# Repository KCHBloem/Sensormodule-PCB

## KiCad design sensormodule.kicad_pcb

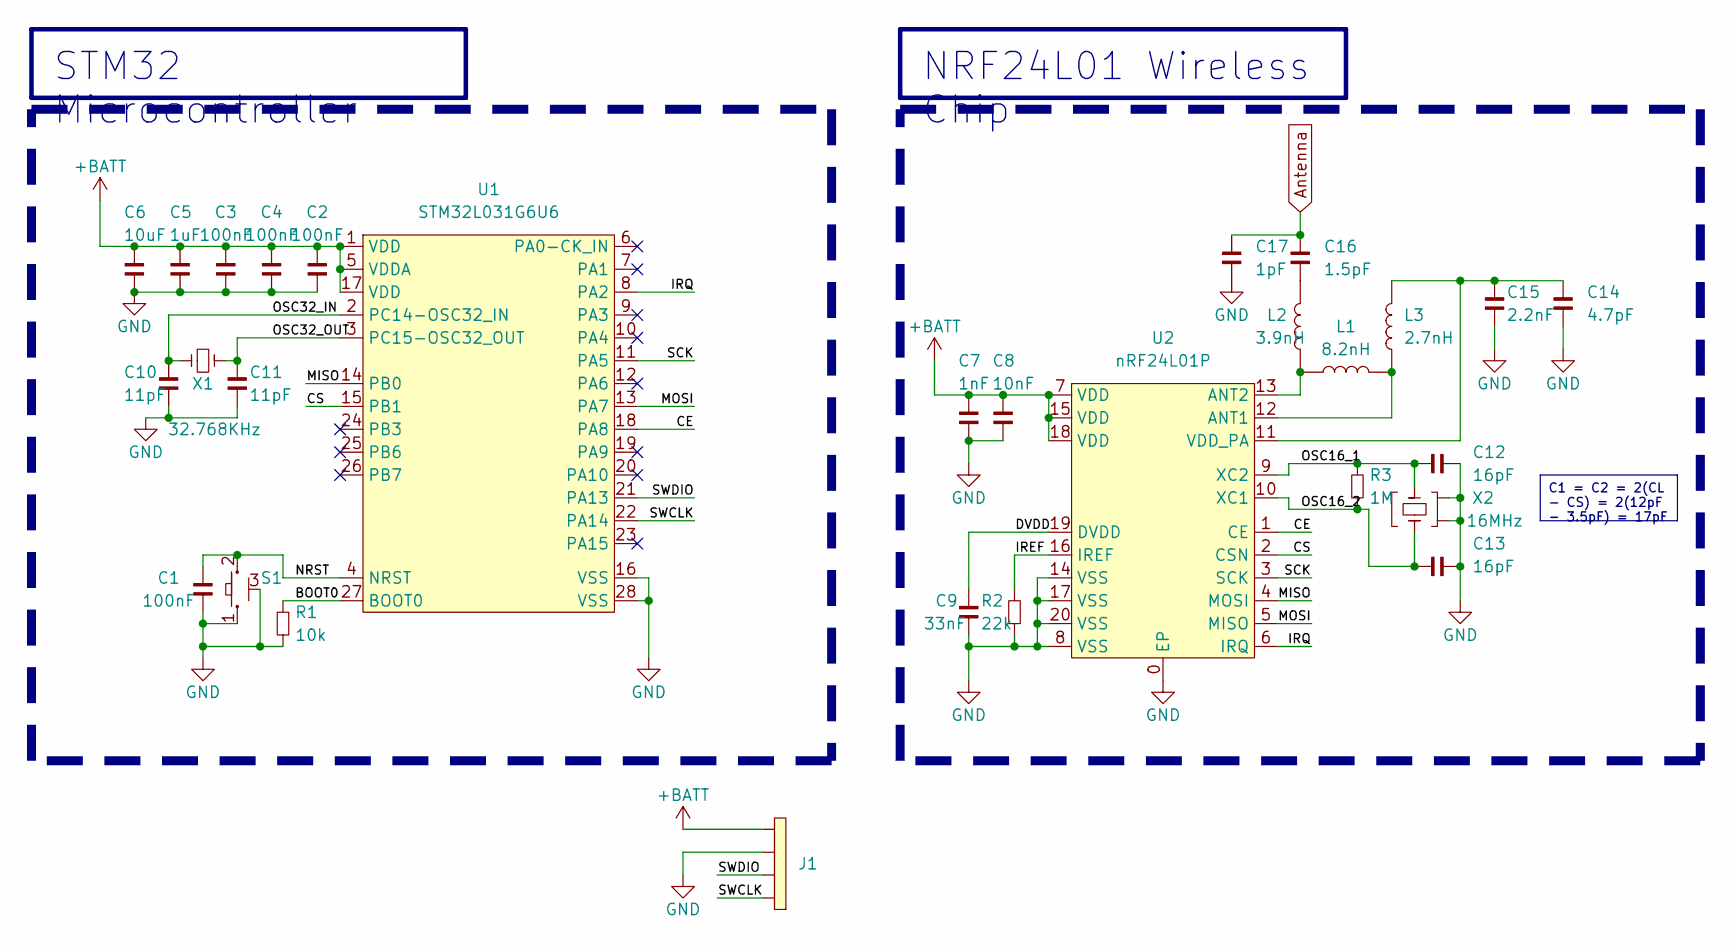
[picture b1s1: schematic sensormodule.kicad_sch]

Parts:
C1, C2, C3, C4: 100nF; [0402] Capacitor; Voltage 16V; Tolerance 10%; Part Number C0402C103K4RACAUTO7411
C5: 1uF; [0402] Capacitor; Voltage 10VDC; Tolerance 10%; Part Number GRM155Z71A105KE01J
C6: 10uF; [0603] Capacitor; Voltage 16VDC; Tolerance 10%; Part Number GRT188R61C106KE13D
C7: 1nF; [0402] Capacitor; Voltage 16V; Tolerance 20%; Part Number C0402C102M4REC7411
C8: 10nF; [0402] Capacitor; Voltage 10V; Tolerance 10%; Part Number C0402C103K8RAC7411
C9: 33nF; [0402] Capacitor; Voltage 16V; Tolerance 10%; Part Number C0402C333K4RECTU
C10, C11: 11pF; [0402] Capacitor; Voltage 50V; Tolerance 10%; Part Number C0402C110K5HACTU
C12, C13: 16pF; [0402] Capacitor; Voltage 50V; Tolerance 2%; Part Number C0402C160G5GACTU
C14: 4.7pF; [0402] Capacitor; Voltage 50V; Tolerance 0.1pF; Part Number CBR04C479B5GACAUTO
C15: 2.2nF; [0402] Capacitor; Voltage 16V; Tolerance 5%; Part Number C0402C222J4GACAUTO
C16: 1.5pF; [0402] Capacitor; Voltage 50V; Tolerance 0.1pF; Part Number CBR04C159B5GACAUTO
C17: 1pF; [0402] Capacitor; Voltage 50V; Tolerance 0.1pF; Part Number CBR04C109B5GACAUTO
J1: [Header]_4-Pos_1.27mm; [Header] 1.27mm 4-Position; Part Number Does not apply
L1: 8.2nH; [0402] Inductor; Part Number LQW15AN8N2J8ZD
L2: 3.9nH; [0402] Inductor; Part Number LQW15AN3N9C00D
L3: 2.7nH; [0402] Inductor; Part Number LQW15AN2N7C00D
R1: 10k; [0402] Resistor; Power Rating 100mW; Tolerance 1%; Part Number ERJ-2RKF1002X
R2: 22k; [0402] Resistor; Power Rating 100 mW; Tolerance 1%; Part Number ERJ-2RKF2202X
R3: 1M; [0402] Resistor; Power Rating 100 mW; Tolerance 5%; Part Number ERJ-U02J105X
S1: RESET; [SW] 4.1mmx2.8mm; Part Number 435441019830
U1: [UFQFPN28]; Part Number STM32L031G6U6
U2: [QFN20]; Part Number nRF24L01P
X1: 32.768KHz; [XTAL] 2.05mmx1.2mm; Part Number FC2012SN 32.768K-70NNA0KC0
X2: 16MHz; [XTAL] 2mmx1.6mm; Part Number FW1600008

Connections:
+BATT: C2.2, C3.2, C4.2, C5.2, C6.2, C7.2, C8.2, J1.4, U1.1 (VDD), U1.5 (VDDA), U1.17 (VDD), U2.7 (VDD), U2.15 (VDD), U2.18 (VDD)
/BOOT0: R1.2, U1.27 (BOOT0)
/CE: U1.18 (PA8), U2.1 (CE)
/CS: U1.15 (PB1), U2.2 (CSN)
/DVDD: C9.2, U2.19 (DVDD)
/IREF: R2.2, U2.16 (IREF)
/IRQ: U1.8 (PA2), U2.6 (IRQ)
/MISO: U1.14 (PB0), U2.4 (MOSI)
/MOSI: U1.13 (PA7), U2.5 (MISO)
/NRST: C1.2, S1.2, U1.4 (NRST)
/OSC16_1: C12.2, R3.2, U2.9 (XC2), X2.3
/OSC16_2: C13.2, R3.1, U2.10 (XC1), X2.1
/OSC32_IN: C10.2, U1.2 (PC14-OSC32_IN), X1.1
/OSC32_OUT: C11.2, U1.3 (PC15-OSC32_OUT), X1.2
/SCK: U1.11 (PA5), U2.3 (SCK)
/SWCLK: J1.1, U1.22 (PA14)
/SWDIO: J1.2, U1.21 (PA13)
Antenna: C16.2, C17.2
GND: C1.1, C2.1, C3.1, C4.1, C5.1, C6.1, C7.1, C8.1, C9.1, C10.1, C11.1, C12.1, C13.1, C14.1, C15.1, C17.1, J1.3, R1.1, R2.1, S1.1, S1.3 (GND), U1.16 (VSS), U1.28 (VSS), U2.0 (EP), U2.8 (VSS), U2.14 (VSS), U2.17 (VSS), U2.20 (VSS), X2.2, X2.4 (GND)
unnamed: C16.1, L2.2
unnamed: L1.2, L3.1, U2.12 (ANT1)
unnamed: L1.1, L2.1, U2.13 (ANT2)
unnamed: C14.2, C15.2, L3.2, U2.11 (VDD_PA)

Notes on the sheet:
NRF24L01 Wireless Chip
C1 = C2 = 2(CL - CS) = 2(12pF - 3.5pF) = 17pF
STM32 Microcontroller

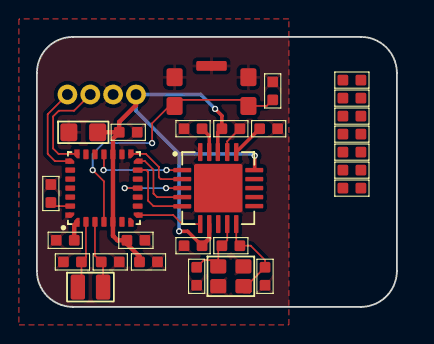
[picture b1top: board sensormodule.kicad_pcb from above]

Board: 4 copper layers, 20.0 x 15.0 mm, 29 parts (0 on the bottom side), 23 nets.
